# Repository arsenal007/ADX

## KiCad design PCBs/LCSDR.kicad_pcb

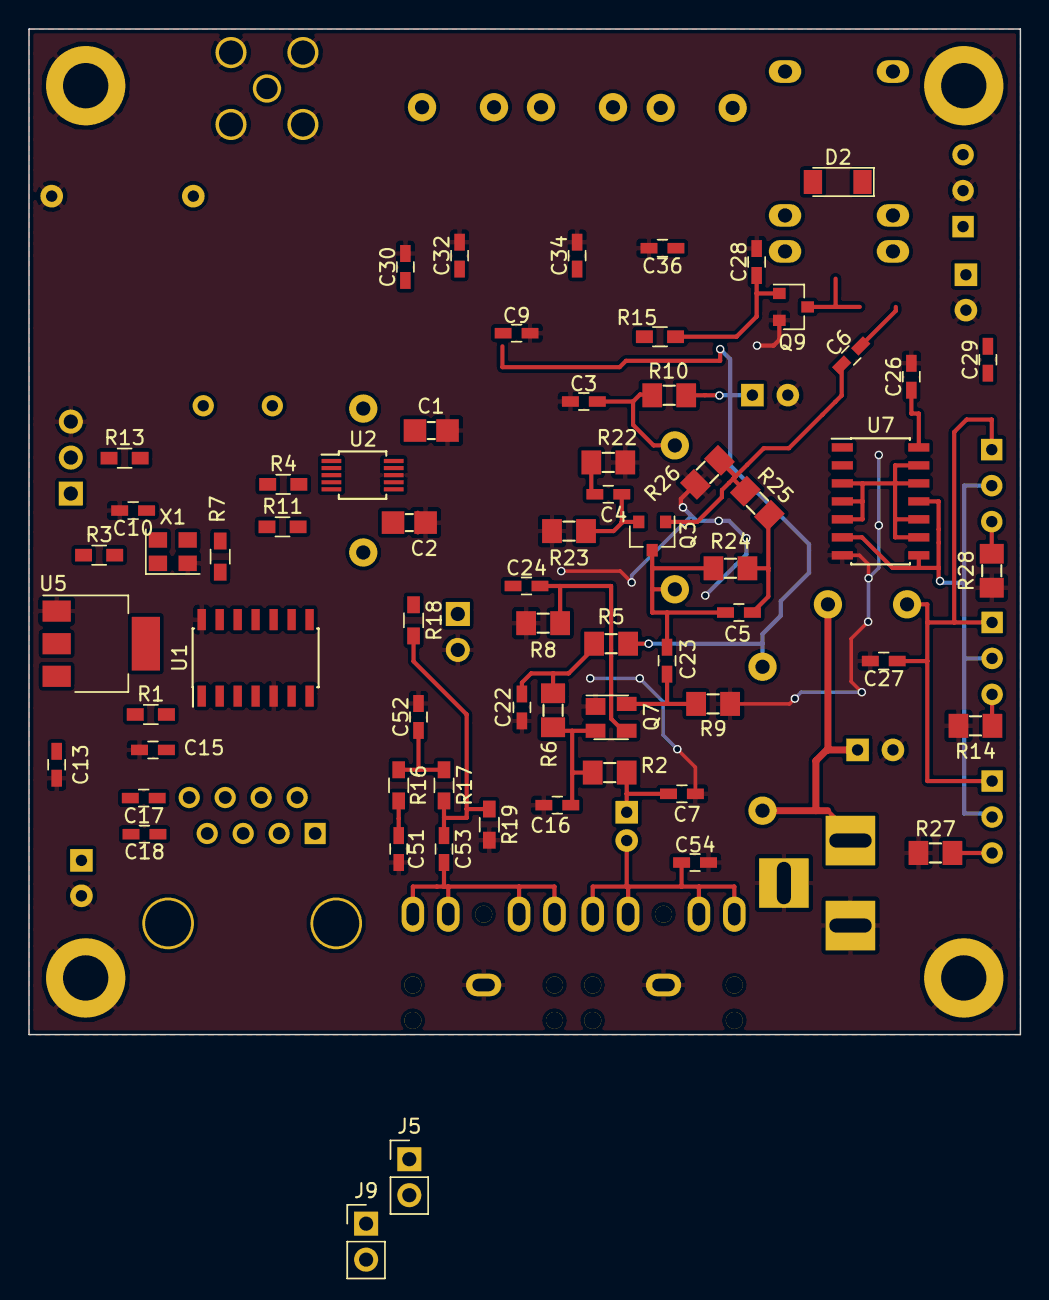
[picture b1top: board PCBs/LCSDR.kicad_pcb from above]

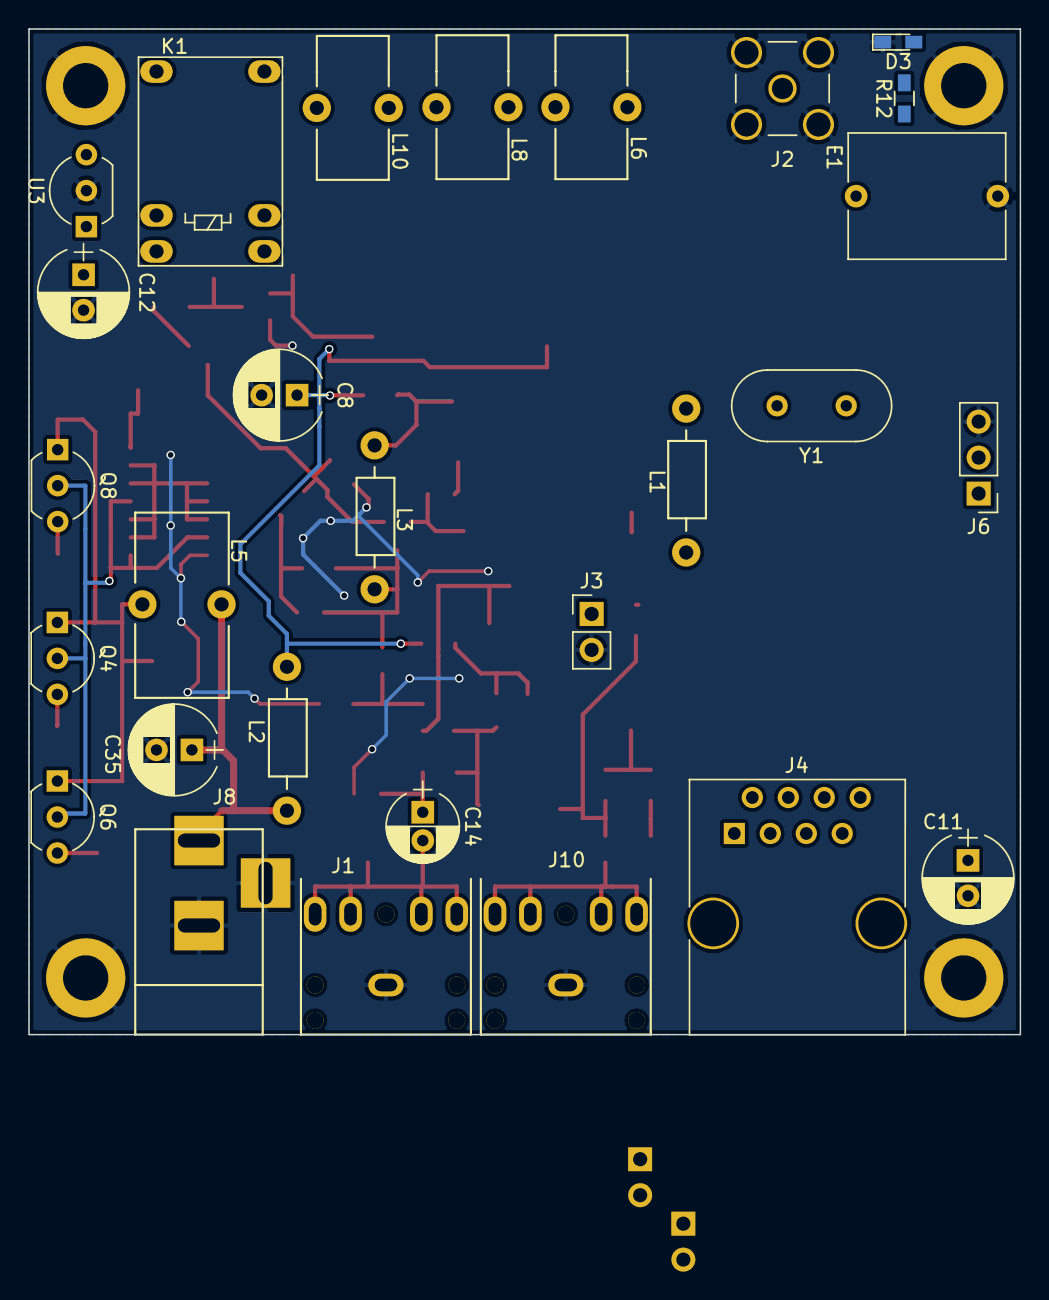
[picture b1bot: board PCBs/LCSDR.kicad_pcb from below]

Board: 2 copper layers, 70.0 x 71.0 mm, 97 parts (28 on the bottom side), 56 nets.

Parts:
C1, C2: 1µF; C_1206_0603
C3, C4, C5, C9, C10, C13, C15, C17, C18, C22, C26, C27, C29, C54: 100nF; C_0603_HandSoldering
C6, C7, C16, C23, C24, C51, C52: 10nF; C_0603_HandSoldering
C8, C11, C12, C35: 100uF; CP_Radial_D6.3mm_P2.50mm
C14: 2.2uF; CP_Radial_D5.0mm_P2.00mm
C28: 15nF; C_0603_HandSoldering
C30, C36: 360pF; C_0603_HandSoldering
C32, C34: 750pF; C_0603_HandSoldering
C53: 1uF; C_0603_HandSoldering
D2: LL4148; D_MiniMELF
D3: LED; LED_0603_HandSoldering
E1: 90V; C_Rect_L11.0mm_W8.8mm_P10.00mm_MKT
J1: MIC; audio_jack_3_5mm_PJ307
J2: ANT; SMA_THT_Jack_Straight
J3: Calibration; Pin_Header_Straight_1x02_Pitch2.54mm
J4: RJ45; RJ45_8
J5, J9: Conn_01x02; Pin_Header_Straight_1x02_Pitch2.54mm
J6: Conn_01x03; Pin_Header_Straight_1x03_Pitch2.54mm
J8: Jack-DC; BARREL_JACK
J10: SPK; audio_jack_3_5mm_PJ307
J12, J13, J14, J15: Conn_01x01; MountingHole_3.2mm_M3_DIN965_Pad
K1: TIANBO-HJR-4102-L; Relay_SPDT_HJR-4102
L1: 100uH; Choke_Horizontal_RM10mm
L2: 33µH; Choke_Horizontal_RM10mm
L3: 5.6uH; Choke_Horizontal_RM10mm
L5: 20uH; Choke_Toroid_6,5x13mm_Vertical
L6, L10: 1.42uH; Choke_Toroid_5x10mm_Vertical
L8: 1.62uH; Choke_Toroid_5x10mm_Vertical
Q3: BFR93A; SOT-23
Q4, Q6, Q8: BS170; TO-92_Inline_Wide
Q7: BF998; SOT-143
Q9: BC849; SOT-23
R1: 0; R_0603_HandSoldering
R2: 2.2K; R_1206_0603
R3, R7, R13: 47; R_0603_HandSoldering
R4, R11: 10K; R_0603_HandSoldering
R5: 100; R_1206_0603
R6: 2.2k; R_1206_0603
R8, R25: 470; R_1206_0603
R9: 27k; R_1206_0603
R10: 33; R_1206_0603
R12: 1k; R_0603_HandSoldering
R14, R27, R28: 1R; R_1206_0603
R15: 3.3k; R_0603_HandSoldering
R16, R17: 10k; R_0603_HandSoldering
R18: 1M; R_0603_HandSoldering
R19: 4.7K; R_0603_HandSoldering
R22: 4.7; R_1206_0603
R23: 47; R_1206_0603
R24: 2.7K; R_1206_0603
R26: 1K; R_1206_0603
U1: ATtiny1614-SS; SOIC-14_3.9x8.7mm_Pitch1.27mm
U2: Si5351; MSOP-10_3x3mm_Pitch0.5mm
U3: L78L05_TO92; TO-92_Inline_Wide
U5: LM1117-3.3; SOT-223-3_TabPin2
U7: 74ACT00; SOIC-14_3.9x8.7mm_Pitch1.27mm
X1: TXC-7C; Oscillator_SMD_Abracon_ASE-4pin_3.2x2.5mm
Y1: 25Mhz; Crystal_HC49-U_Vertical

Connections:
+3V3: C1.1, C10.1, C11.1, C13.1, L1.1, R1.1, R4.1, R11.1, R18.1, U2.1, U5.2, X1.4
+12V: C8.1, C9.1, D2.1, K1.5, L2.1, R5.2, R10.2, U3.3, U5.3
+12VA: C35.1, J8.1, L2.2, L5.1
AUDIO_IN: C51.1, R16.1, U1.4
CLK0: U2.10, U7.1
CLK1: C24.2, U2.9
GND: C1.2, C2.1, C3.2, C7.2, C8.2, C9.2, C10.2, C11.2, C12.2, C13.2, C15.2, C16.2, C22.2, C26.2, C27.2, C28.2, C30.2, C32.2, C34.2, C35.2, C36.2, C51.2, C52.2, C54.2, D3.1, E1.2, J1.1, J2.2, J3.2, J5.2, J6.3, J8.2, J8.3, J9.2, J10.1, J12.1, J13.1, J14.1, J15.1, Q7.1, Q9.2, R8.2, R9.2, R14.2, R19.2, R22.2, R23.2, R26.2, R27.2, R28.2, U1.5, U1.14, U2.8, U3.2, U5.1, U7.7, X1.2
LED: R12.1, U1.3
LPF: C36.1, J9.1, K1.1, K1.12, L10.2
unnamed: C2.2, L1.2, U2.7
unnamed: C3.1, L3.1, R10.1
unnamed: C4.1, R22.1
unnamed: C4.2, Q3.2, R23.1
unnamed: C5.2, R24.2, R25.1
unnamed: C6.1, Q3.1, R25.2, R26.1
unnamed: C7.1, C14.1, R2.2
unnamed: C14.2, C54.1, J1.2, J1.3, J1.4, J1.5
unnamed: C16.1, Q7.2, R2.1, R6.1
unnamed: C17.1, J4.8
unnamed: C18.1, J4.7
unnamed: C22.1, R5.1, R6.2
unnamed: C23.1, Q7.4, R9.1
unnamed: C5.1, C23.2, L3.2, Q3.3, R24.1
unnamed: C24.1, Q7.3, R8.1
unnamed: C27.1, C29.1, L5.2, Q4.1, Q6.1, Q8.1
unnamed: C28.1, Q9.1, R15.1
unnamed: C29.2, K1.6
unnamed: C30.1, E1.1, J2.1, J5.1, L6.1
unnamed: C32.1, L6.2, L8.1
unnamed: C34.1, L8.2, L10.1
unnamed: C52.1, R16.2, R17.1
unnamed: C53.1, J10.2, J10.3, J10.4, J10.5
unnamed: C53.2, R17.2, R18.2, R19.1
unnamed: D2.2, K1.8, Q9.3
unnamed: D3.2, R12.2
unnamed: J3.1, U2.6
unnamed: J4.3, U1.7
unnamed: J4.6, U1.6
unnamed: J6.1, R3.1
unnamed: J6.2, R13.1
unnamed: Q4.2, Q6.2, Q8.2, U7.6, U7.8, U7.11
unnamed: Q4.3, R14.1
unnamed: Q6.3, R27.1
unnamed: Q8.3, R28.1
unnamed: R7.1, U1.13
unnamed: R7.2, X1.3
unnamed: U2.2, Y1.2
unnamed: U2.3, Y1.1
unnamed: U7.3, U7.4, U7.5, U7.9, U7.10, U7.12, U7.13
RESET_UPDI: C17.2, C18.2, R13.2, U1.10
RF_IN: C6.2, K1.7
RX_TX: R15.2, U1.11
RX_TX_PA: U1.12, U7.2
SCL: R4.2, U1.9, U2.4
SDA: R11.2, U1.8, U2.5
VCC: C12.1, C15.1, C26.1, R1.2, R3.2, U1.1, U3.1, U7.14

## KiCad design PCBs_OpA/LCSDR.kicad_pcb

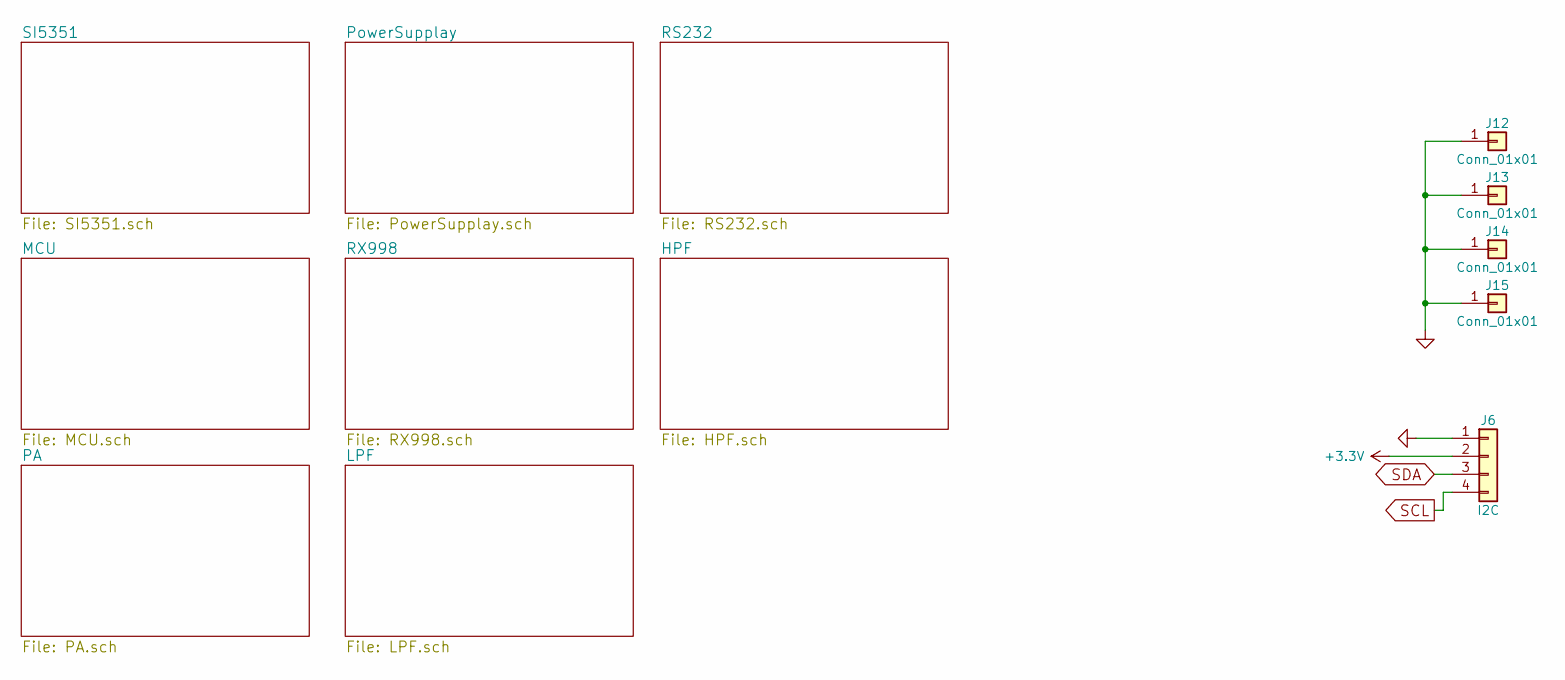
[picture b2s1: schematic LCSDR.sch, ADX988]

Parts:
J6: I2C; Pin_Header_Straight_1x04_Pitch2.54mm
J12, J13, J14, J15: Conn_01x01; MountingHole_3.2mm_M3_DIN965_Pad

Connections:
+3V3: J6.2; also elsewhere on the board
GND: J6.1, J12.1, J13.1, J14.1, J15.1; also elsewhere on the board
SCL: J6.4; also elsewhere on the board
SDA: J6.3; also elsewhere on the board

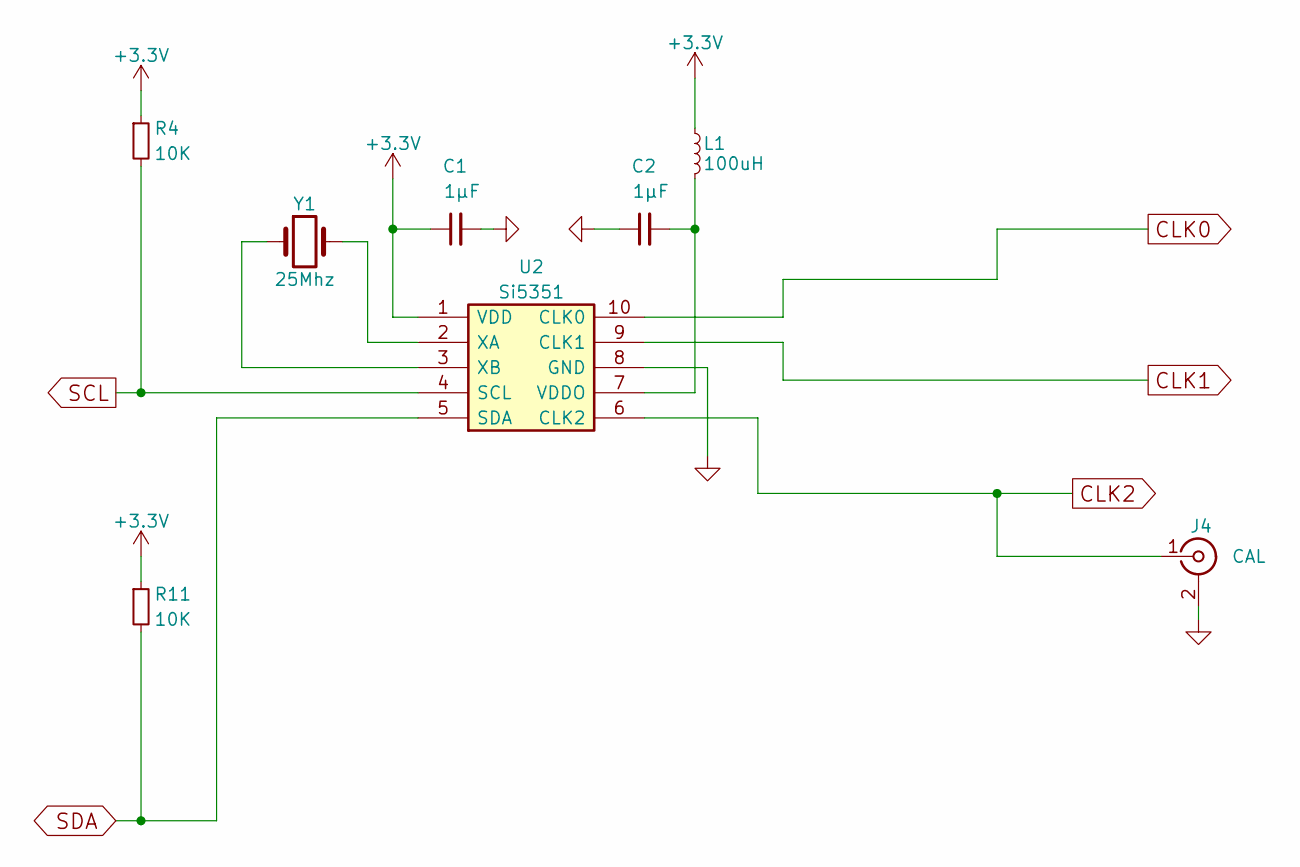
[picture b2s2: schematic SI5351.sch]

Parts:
C1, C2: 1µF; C_1206_0603
J4: CAL; U.FL_Molex_MCRF_73412-0110_Vertical
L1: 100uH; R_Axial_DIN0207_L6.3mm_D2.5mm_P10.16mm_Horizontal
R4, R11: 10K; R_1206_0603
U2: Si5351; MSOP-10_3x3mm_Pitch0.5mm
Y1: 25Mhz; Crystal_SMD_HC49-SD

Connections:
+3V3: C1.1, L1.1, R4.1, R11.1, U2.1 (VDD); also elsewhere on the board
CLK0: U2.10 (CLK0); also elsewhere on the board
CLK1: U2.9 (CLK1); also elsewhere on the board
CLK2: J4.1 (In), U2.6 (CLK2); also elsewhere on the board
GND: C1.2, C2.1, J4.2 (Ext), U2.8 (GND); also elsewhere on the board
unnamed: C2.2, L1.2, U2.7 (VDDO)
unnamed: U2.2 (XA), Y1.2
unnamed: U2.3 (XB), Y1.1
SCL: R4.2, U2.4 (SCL); also elsewhere on the board
SDA: R11.2, U2.5 (SDA); also elsewhere on the board

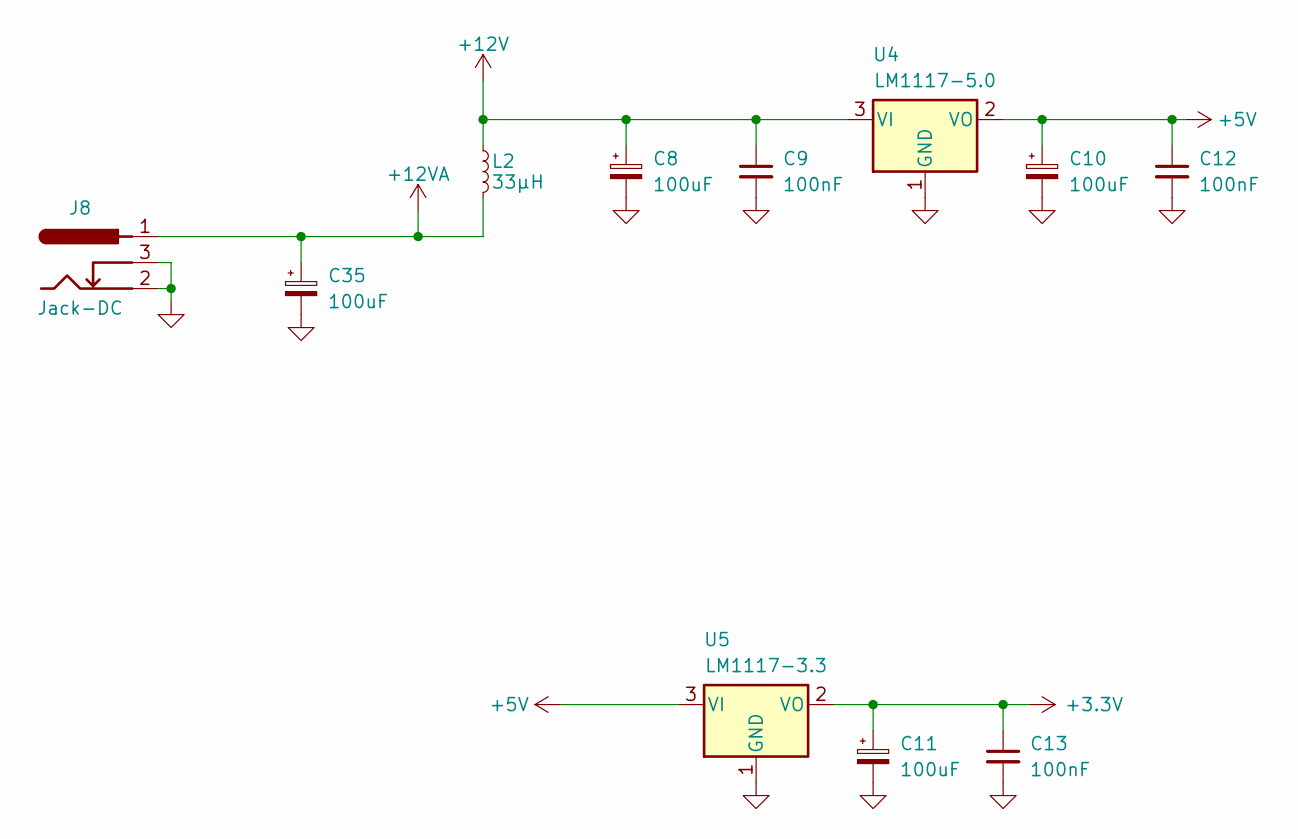
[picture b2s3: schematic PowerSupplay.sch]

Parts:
C8, C10, C11, C35: 100uF; CP_Radial_D6.3mm_P2.50mm
C9, C12, C13: 100nF; C_1206_0603
J8: Jack-DC; BARREL_JACK
L2: 33µH; Choke_Horizontal_RM10mm
U4: LM1117-5.0; SOT-223-3_TabPin2
U5: LM1117-3.3; SOT-223-3_TabPin2

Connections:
+3V3: C11.1, C13.1, U5.2 (VO); also elsewhere on the board
+5V: C10.1, C12.1, U4.2 (VO), U5.3 (VI); also elsewhere on the board
+12V: C8.1, C9.1, L2.1, U4.3 (VI); also elsewhere on the board
+12VA: C35.1, J8.1, L2.2; also elsewhere on the board
GND: C8.2, C9.2, C10.2, C11.2, C12.2, C13.2, C35.2, J8.2, J8.3, U4.1 (GND), U5.1 (GND); also elsewhere on the board

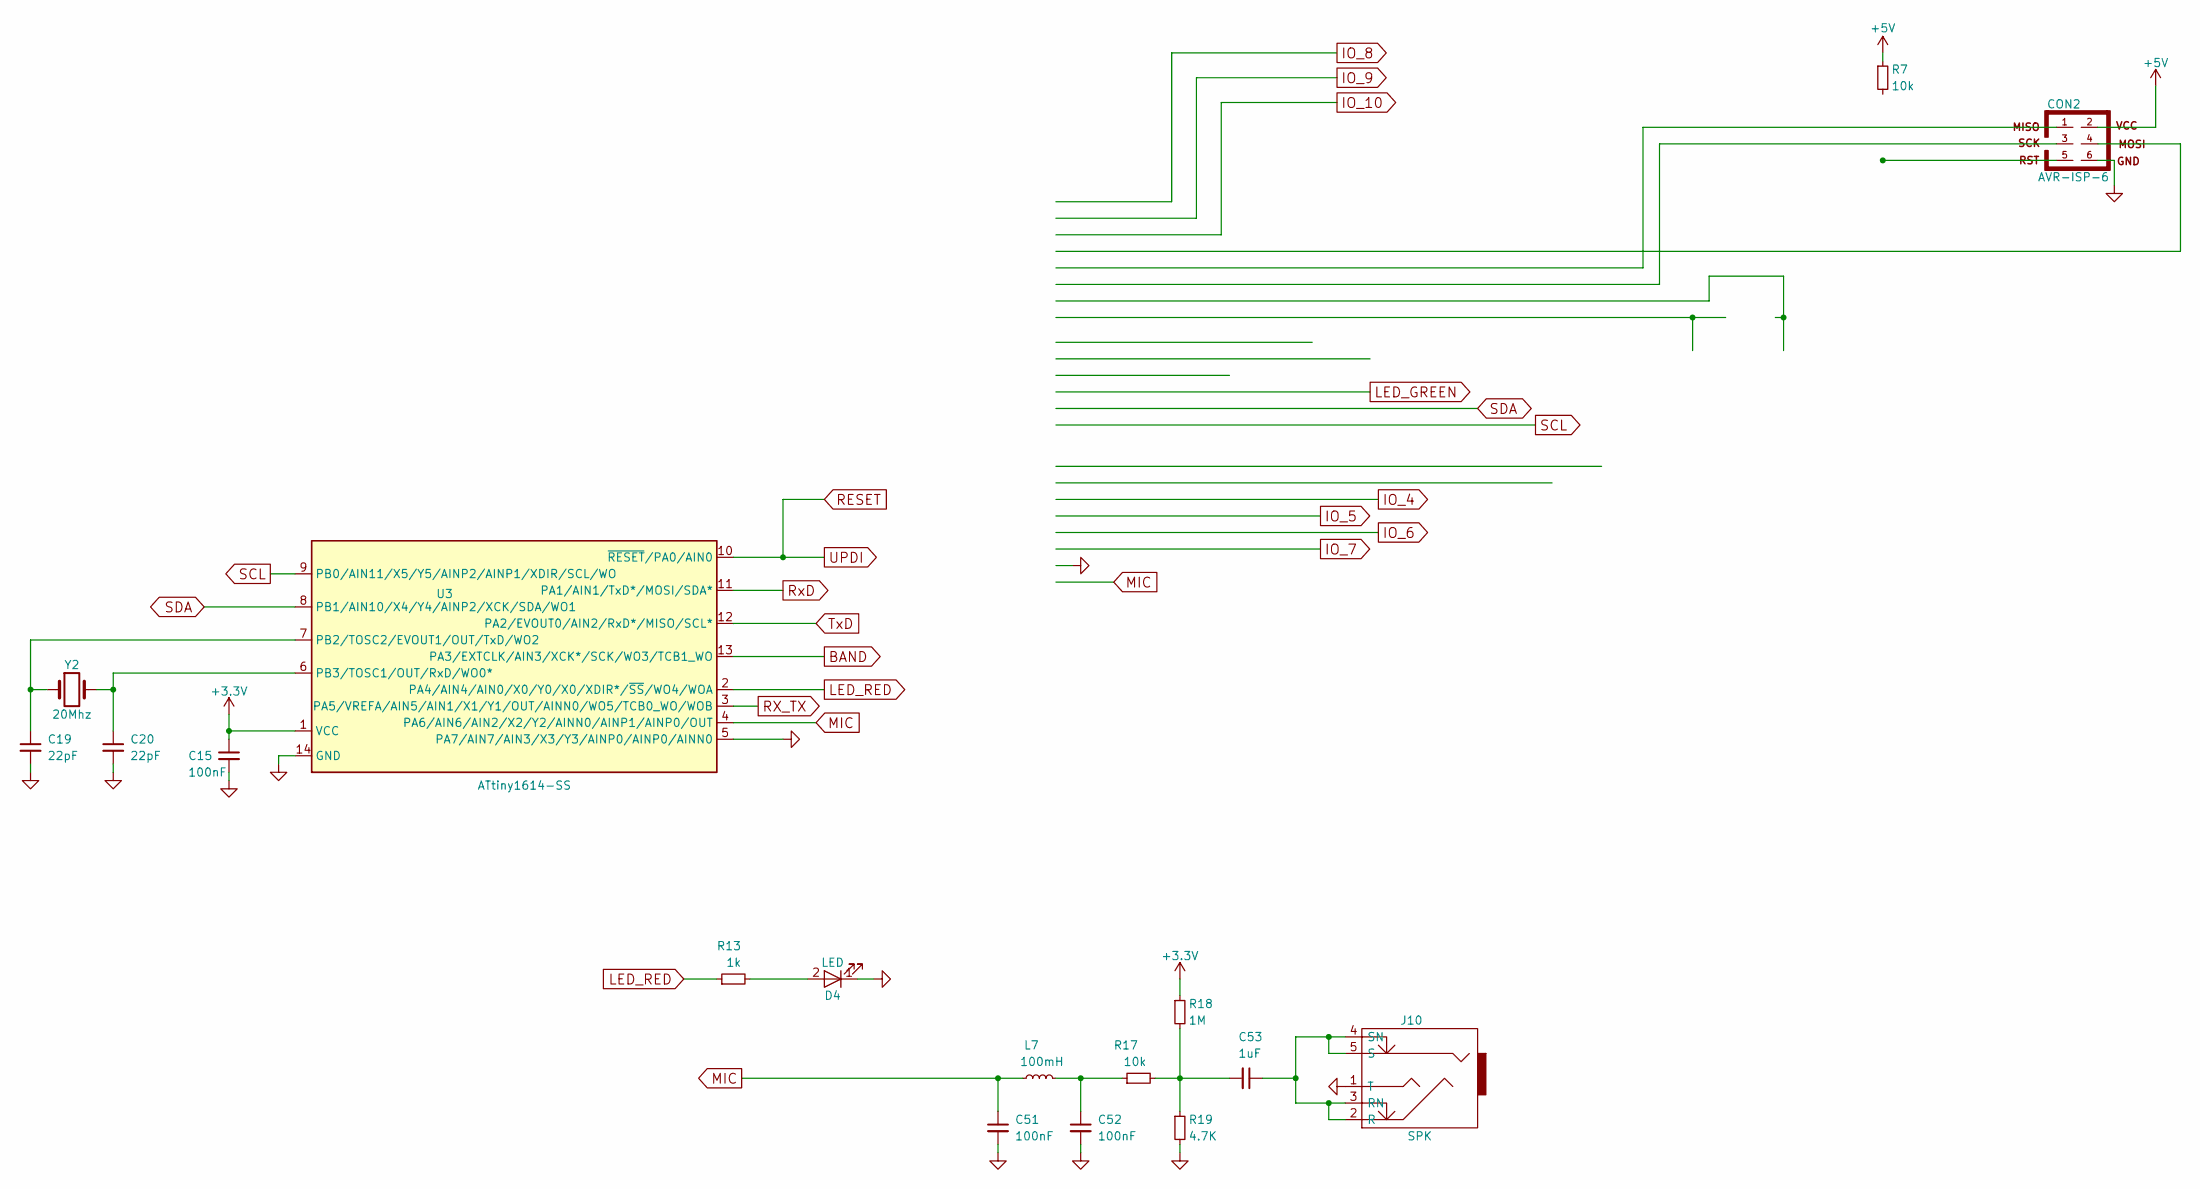
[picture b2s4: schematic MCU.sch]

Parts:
C15, C51, C52: 100nF; C_1206_0603
C19, C20: 22pF; C_1206_0603
C53: 1uF; C_1206_0603
CON2: AVR-ISP-6; IDC-Header_2x03_Pitch2.54mm_Straight
D4: LED; LED_D3.0mm_Horizontal_O3.81mm_Z10.0mm
J10: SPK; audio_jack_3_5mm_PJ307
L7: 100mH; Choke_Toroid_8x16mm_Vertical
R7, R17: 10k; R_1206_0603
R13: 1k; R_1206_0603
R18: 1M; R_1206_0603
R19: 4.7K; R_1206_0603
U3: ATtiny1614-SS; SOIC-14_3.9x8.7mm_Pitch1.27mm
Y2: 20Mhz; Crystal_HC49-U_Vertical

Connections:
+3V3: C15.1, R18.1, U3.1 (VCC); also elsewhere on the board
+5V: CON2.2, R7.1; also elsewhere on the board
GND: C15.2, C19.2, C20.2, C51.2, C52.2, CON2.6, D4.1 (K), J10.1 (T), R19.2, U3.5 (PA7/AIN7/AIN3/X3/Y3/AINP0/AINP0/AINN0), U3.14 (GND); also elsewhere on the board
LED_RED: R13.1, U3.2 (PA4/AIN4/AIN0/X0/Y0/X0/XDIR*/~SS~/WO4/W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)
MIC: C51.1, L7.1, U3.4 (PA6/AIN6/AIN2/X2/Y2/AINN0/AINP1/AINP0/O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)
unnamed: C19.1, U3.7 (PB2/TOSC2/EVOUT1/OUT/TxD/WO2), Y2.1
unnamed: C20.1, U3.6 (PB3/TOSC1/OUT/RxD/WO0*), Y2.2
unnamed: C52.1, L7.2, R17.1
unnamed: C53.1, J10.2 (R), J10.3 (RN), J10.4 (SN), J10.5 (S)
unnamed: C53.2, R17.2, R18.2, R19.1
unnamed: D4.2 (A), R13.2
RESET: U3.10 (~RESET~/PA0/AIN0); also elsewhere on the board
RX_TX: U3.3 (PA5/VREFA/AIN5/AIN1/X1/Y1/OUT/AINN0/WO5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); also elsewhere on the board
RxD: U3.11 (PA1/AIN1/TxD*/MOSI/SDA*); also elsewhere on the board
SCL: U3.9 (PB0/AIN11/X5/Y5/AINP2/AINP1/XDIR/SCL/WO); also elsewhere on the board
SDA: U3.8 (PB1/AIN10/X4/Y4/AINP2/XCK/SDA/WO1); also elsewhere on the board
TxD: U3.12 (PA2/EVOUT0/AIN2/RxD*/MISO/SCL*); also elsewhere on the board

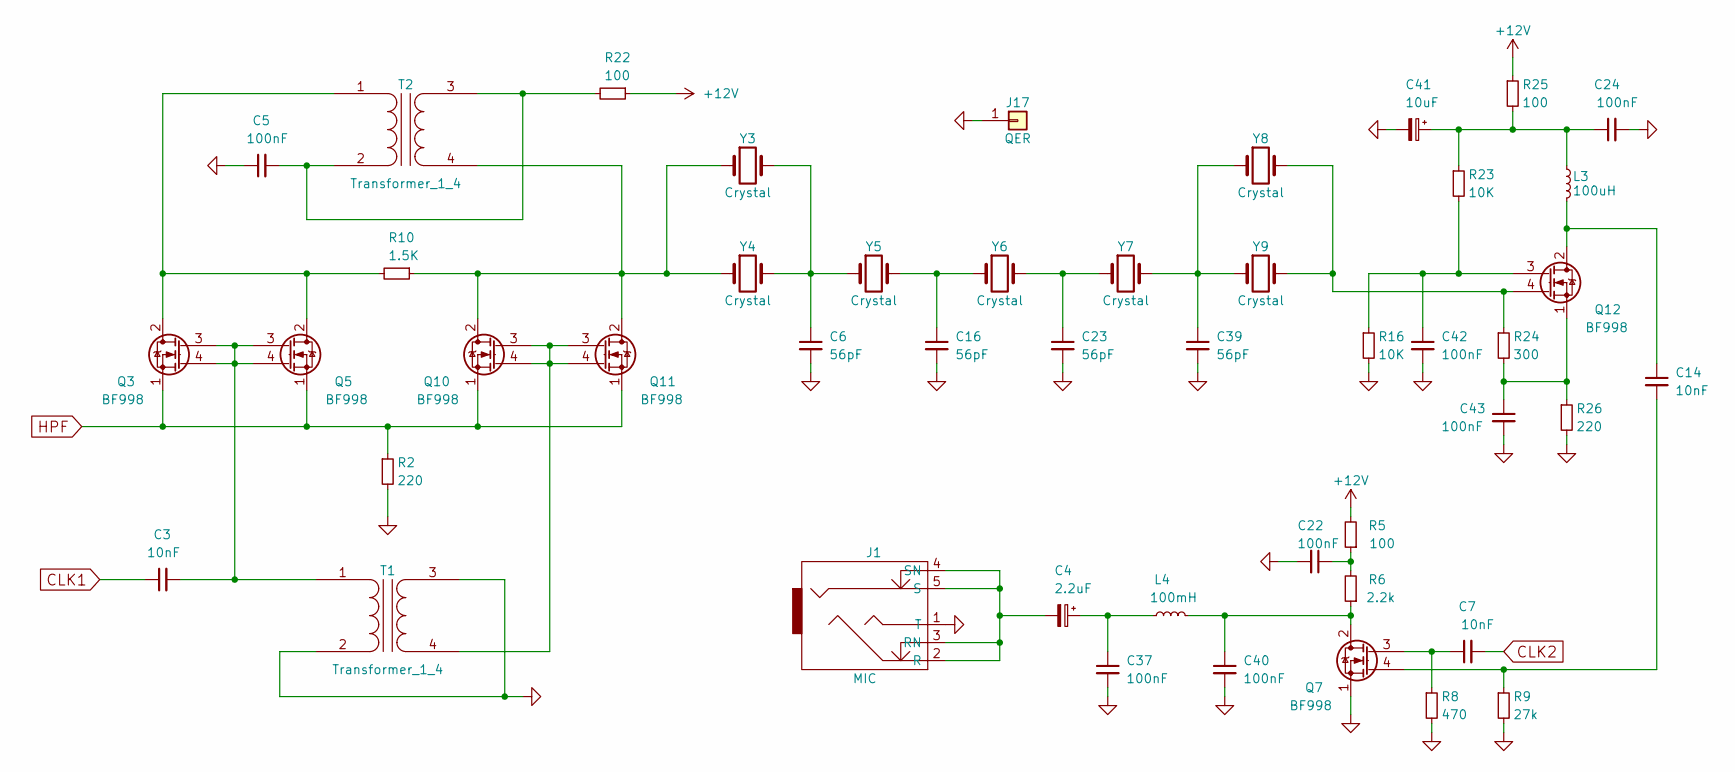
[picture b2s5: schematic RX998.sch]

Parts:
C3, C7, C14: 10nF; C_1206_0603
C4: 2.2uF; CP_Radial_D5.0mm_P2.00mm
C5, C22, C24, C37, C40, C42, C43: 100nF; C_1206_0603
C6, C16, C23, C39: 56pF; C_1206_0603
C41: 10uF; CP_Radial_D5.0mm_P2.00mm
J1: MIC; audio_jack_3_5mm_PJ307
J17: QER; Pin_Header_Straight_1x01_Pitch2.54mm
L3: 100uH; Choke_Horizontal_RM10mm
L4: 100mH; Choke_Toroid_8x16mm_Vertical
Q3, Q5, Q7, Q10, Q11, Q12: BF998; SOT-143
R2, R26: 220; R_1206_0603
R5, R22, R25: 100; R_1206_0603
R6: 2.2k; R_1206_0603
R8: 470; R_1206_0603
R9: 27k; R_1206_0603
R10: 1.5K; R_1206_0603
R16, R23: 10K; R_1206_0603
R24: 300; R_1206_0603
T1, T2: Transformer_1_4; TF14
Y3, Y4, Y5, Y6, Y7, Y8, Y9: Crystal; Crystal_HC49-U_Vertical

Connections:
+12V: R5.2, R22.1, R25.1; also elsewhere on the board
CLK1: C3.1; also elsewhere on the board
CLK2: C7.2; also elsewhere on the board
GND: C5.1, C6.2, C16.2, C22.2, C23.2, C24.2, C37.2, C39.2, C40.2, C41.2, C42.2, C43.2, J1.1 (T), J17.1, Q7.1 (S), R2.2, R8.2, R9.2, R16.2, R26.2, T1.2 (AB), T1.3; also elsewhere on the board
HPF: Q3.1 (S), Q5.1 (S), Q10.1 (S), Q11.1 (S), R2.1; also elsewhere on the board
unnamed: C3.2, Q3.3 (G2), Q3.4 (G1), Q5.3 (G2), Q5.4 (G1), T1.1 (AA)
unnamed: C4.2, J1.2 (R), J1.3 (RN), J1.4 (SN), J1.5 (S)
unnamed: C5.2, R22.2, T2.2 (AB), T2.3
unnamed: C6.1, Y3.2, Y4.2, Y5.1
unnamed: C7.1, Q7.3 (G2), R8.1
unnamed: C14.1, L3.2, Q12.2 (D)
unnamed: C14.2, Q7.4 (G1), R9.1
unnamed: C16.1, Y5.2, Y6.1
unnamed: C22.1, R5.1, R6.2
unnamed: C23.1, Y6.2, Y7.1
unnamed: C24.1, C41.1, L3.1, R23.1, R25.2
unnamed: C4.1, C37.1, L4.1
unnamed: C39.1, Y7.2, Y8.1, Y9.1
unnamed: C40.1, L4.2, Q7.2 (D), R6.1
unnamed: C42.1, Q12.3 (G2), R16.1, R23.2
unnamed: C43.1, Q12.1 (S), R24.2, R26.1
unnamed: Q3.2 (D), Q5.2 (D), R10.2, T2.1 (AA)
unnamed: Q10.2 (D), Q11.2 (D), R10.1, T2.4, Y3.1, Y4.1
unnamed: Q10.3 (G2), Q10.4 (G1), Q11.3 (G2), Q11.4 (G1), T1.4
unnamed: Q12.4 (G1), R24.1, Y8.2, Y9.2

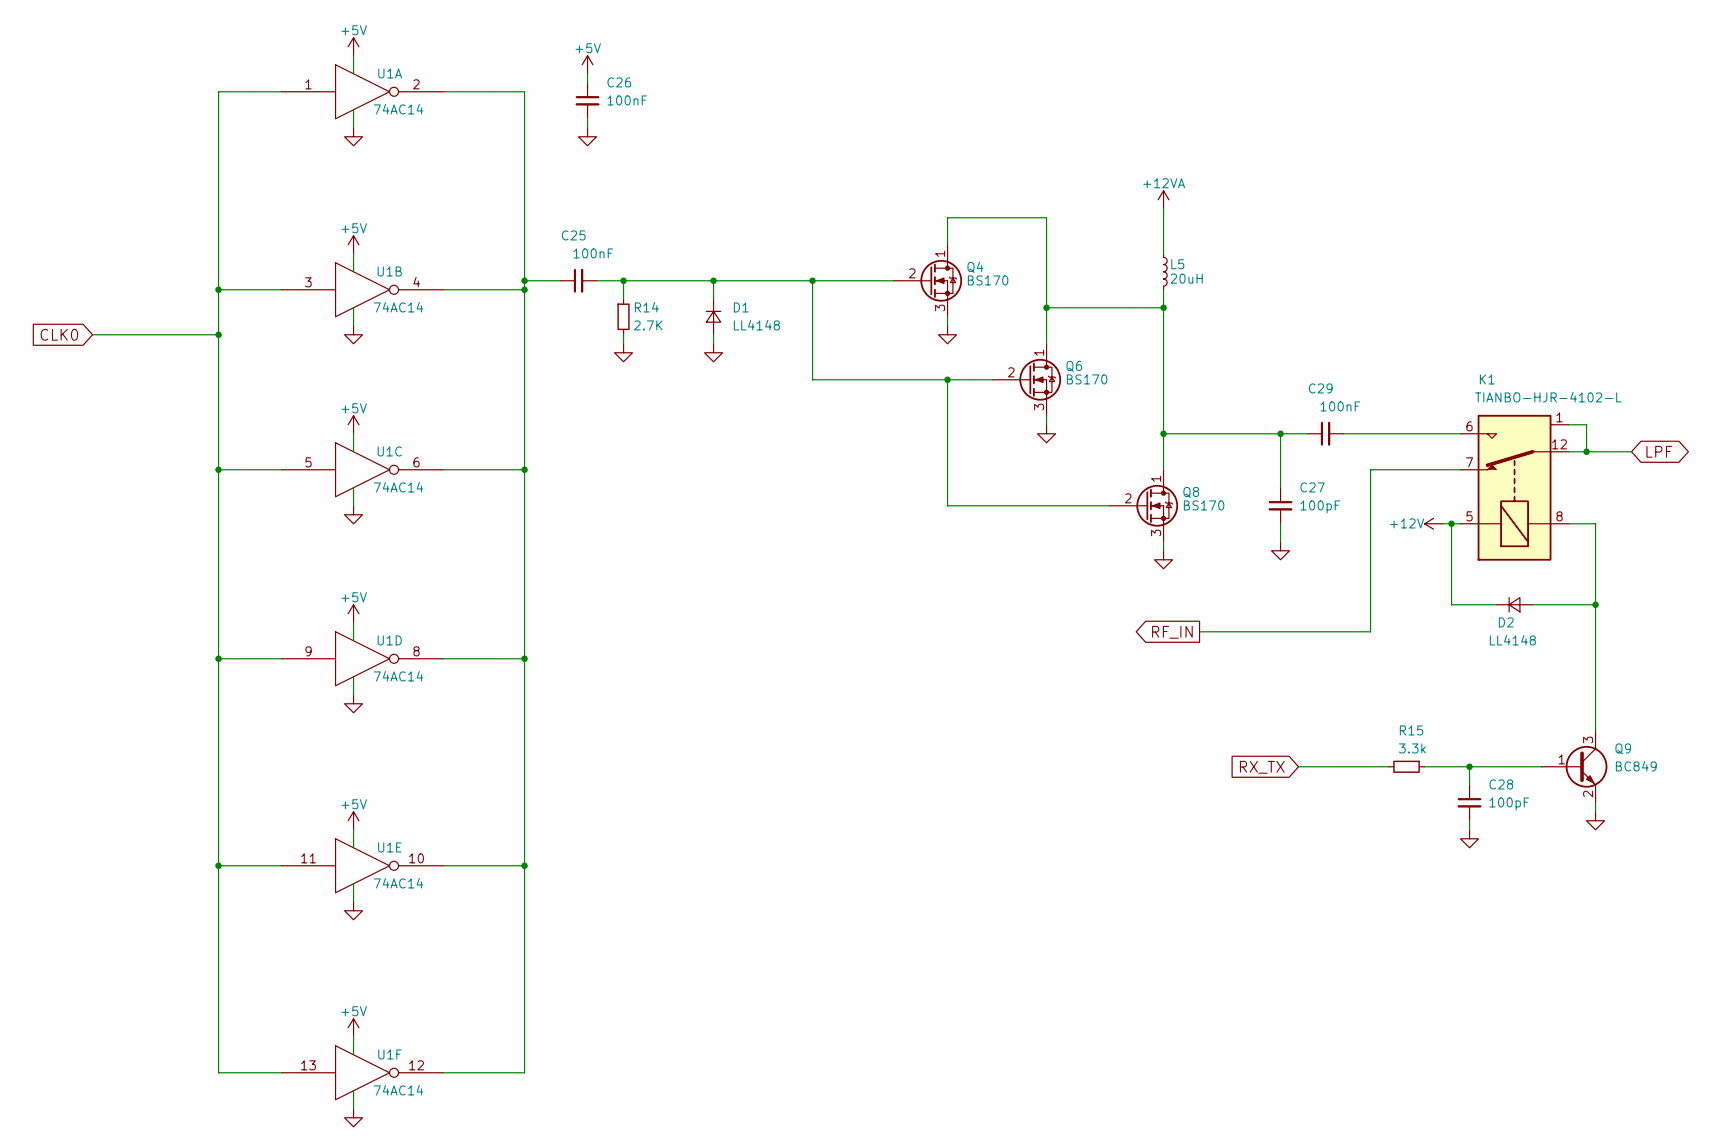
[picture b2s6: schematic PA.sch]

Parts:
C25, C26, C29: 100nF; C_1206_0603
C27: 100pF; C_Disc_D4.7mm_W2.5mm_P5.00mm
C28: 100pF; C_1206_0603
D1, D2: LL4148; D_MiniMELF
K1: TIANBO-HJR-4102-L; Relay_SPDT_HJR-4102
L5: 20uH; Choke_Toroid_6,5x13mm_Vertical
Q4, Q6, Q8: BS170; TO-92_Inline_Wide
Q9: BC849; SOT-23
R14: 2.7K; R_1206_0603
R15: 3.3k; R_1206_0603
U1: 74AC14; DIP-14_W7.62mm_LongPads

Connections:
+5V: C26.1, U1.14 (VCC); also elsewhere on the board
+12V: D2.1 (K), K1.5; also elsewhere on the board
+12VA: L5.1; also elsewhere on the board
CLK0: U1.1, U1.3, U1.5, U1.9, U1.11, U1.13; also elsewhere on the board
GND: C26.2, C27.2, C28.2, D1.2 (A), Q4.3 (S), Q6.3 (S), Q8.3 (S), Q9.2 (E), R14.2, U1.7 (GND); also elsewhere on the board
LPF: K1.1, K1.12; also elsewhere on the board
unnamed: C25.1, U1.2, U1.4, U1.6, U1.8, U1.10, U1.12
unnamed: C25.2, D1.1 (K), Q4.2 (G), Q6.2 (G), Q8.2 (G), R14.1
unnamed: C27.1, C29.1, L5.2, Q4.1 (D), Q6.1 (D), Q8.1 (D)
unnamed: C28.1, Q9.1 (B), R15.1
unnamed: C29.2, K1.6
unnamed: D2.2 (A), K1.8, Q9.3 (C)
RF_IN: K1.7; also elsewhere on the board
RX_TX: R15.2; also elsewhere on the board

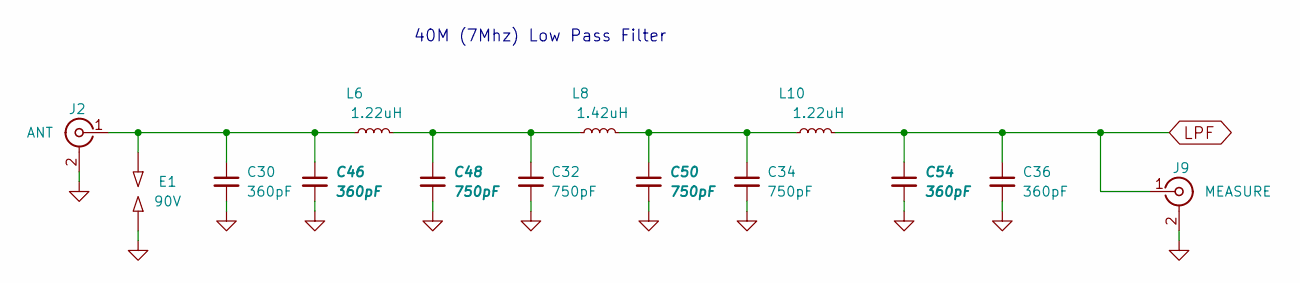
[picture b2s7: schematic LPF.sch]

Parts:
C30, C36: 360pF; C_Disc_D4.7mm_W2.5mm_P5.00mm
C32, C34: 750pF; C_Disc_D4.7mm_W2.5mm_P5.00mm
C46, C54: 360pF; C_1206_0603
C48, C50: 750pF; C_1206_0603
E1: 90V; C_Rect_L11.0mm_W8.8mm_P10.00mm_MKT
J2: ANT; SMA_THT_Jack_Straight
J9: MEASURE; U.FL_Molex_MCRF_73412-0110_Vertical
L6, L10: 1.22uH; Choke_Toroid_6,5x13mm_Vertical
L8: 1.42uH; Choke_Toroid_6,5x13mm_Vertical

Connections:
GND: C30.2, C32.2, C34.2, C36.2, C46.2, C48.2, C50.2, C54.2, E1.2, J2.2 (Ext), J9.2 (Ext); also elsewhere on the board
LPF: C36.1, C54.1, J9.1 (In), L10.2; also elsewhere on the board
unnamed: C30.1, C46.1, E1.1, J2.1 (In), L6.1
unnamed: C32.1, C48.1, L6.2, L8.1
unnamed: C34.1, C50.1, L8.2, L10.1

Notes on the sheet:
40M (7Mhz) Low Pass Filter

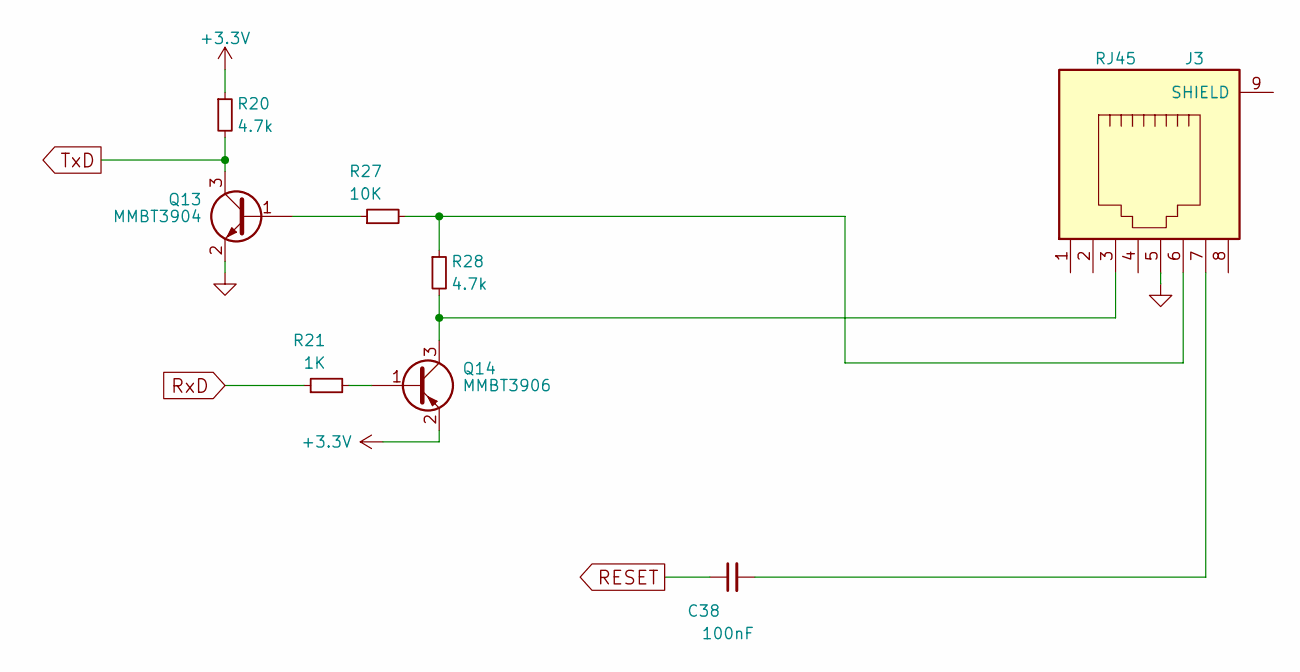
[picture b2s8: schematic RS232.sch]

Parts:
C38: 100nF; C_1206_0603
J3: RJ45; RJ45_8
Q13: MMBT3904; SOT-23
Q14: MMBT3906; SOT-23
R20, R28: 4.7k; R_0603_HandSoldering
R21: 1K; R_0603_HandSoldering
R27: 10K; R_0603_HandSoldering

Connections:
+3V3: Q14.2 (E), R20.1; also elsewhere on the board
GND: J3.5, Q13.2 (E); also elsewhere on the board
unnamed: C38.2, J3.7
unnamed: J3.3, Q14.3 (C), R28.2
unnamed: J3.6, R27.2, R28.1
unnamed: Q13.1 (B), R27.1
unnamed: Q14.1 (B), R21.2
RESET: C38.1; also elsewhere on the board
RxD: R21.1; also elsewhere on the board
TxD: Q13.3 (C), R20.2; also elsewhere on the board

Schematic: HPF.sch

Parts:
C21, C49: 680pF; C_1206_0603
C45, C47: 270pF; C_1206_0603
J5, J7: MEASURE; U.FL_Molex_MCRF_73412-0110_Vertical
L13, L17: 900nH; Choke_Toroid_6,5x13mm_Vertical
L15: 800nH; Choke_Toroid_6,5x13mm_Vertical

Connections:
GND: J5.2 (Ext), J7.2 (Ext), L13.2, L15.2, L17.2; also elsewhere on the board
HPF: C49.2, J7.1 (In); also elsewhere on the board
unnamed: C21.2, C45.1, L13.1
unnamed: C45.2, C47.1, L15.1
unnamed: C47.2, C49.1, L17.1
RF_IN: C21.1, J5.1 (In); also elsewhere on the board

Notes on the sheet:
40M (7Mhz) High Pass Filter

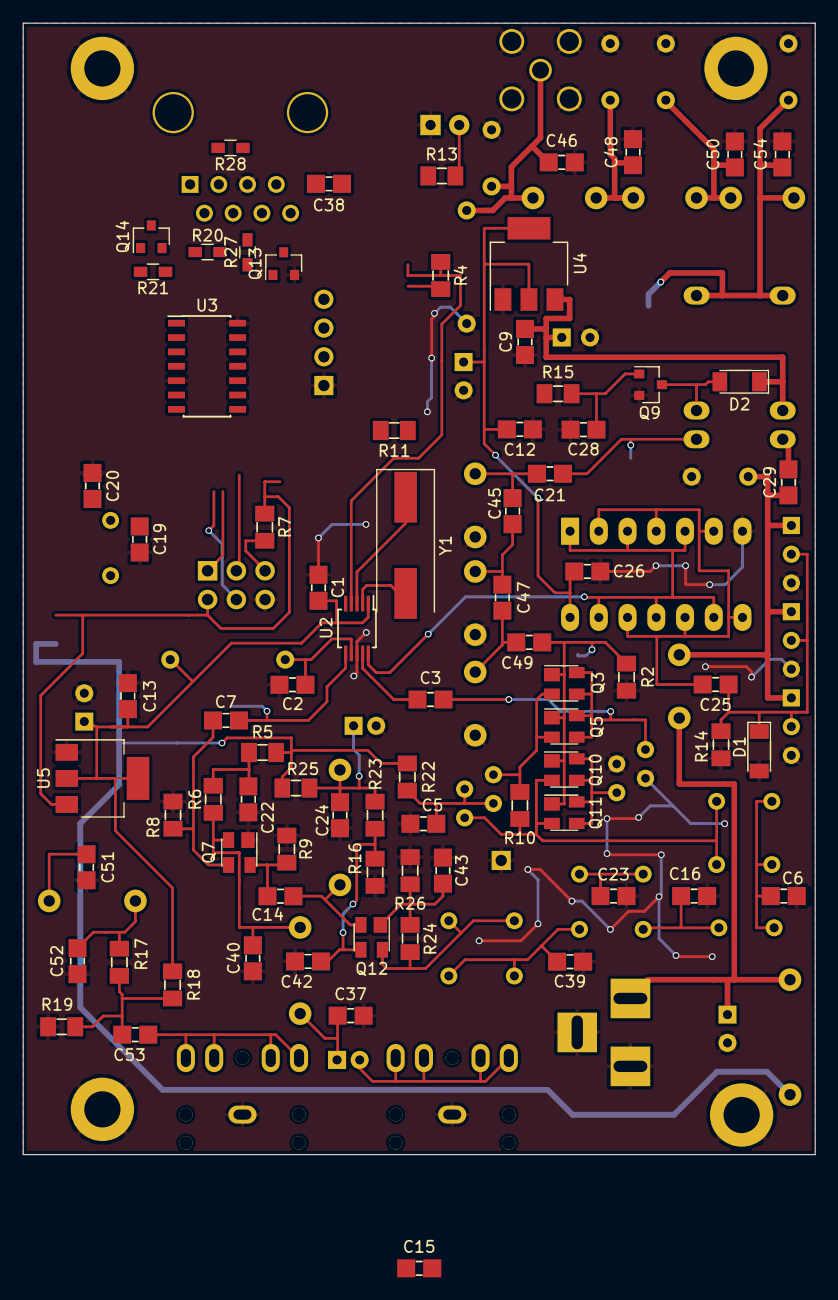
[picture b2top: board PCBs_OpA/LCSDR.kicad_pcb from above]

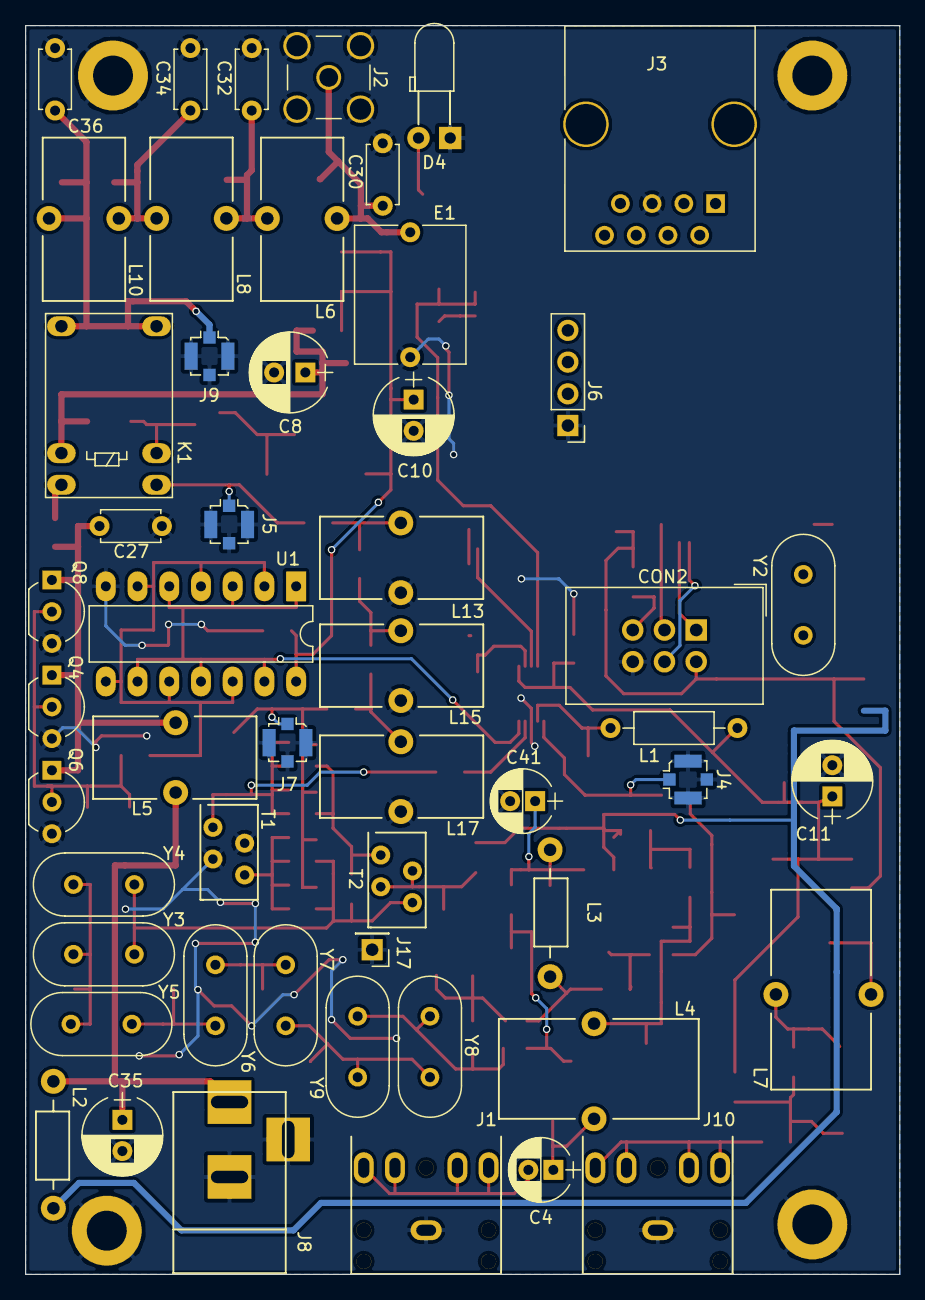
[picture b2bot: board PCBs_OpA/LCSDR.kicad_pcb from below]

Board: 2 copper layers, 70.0 x 100.0 mm, 135 parts (52 on the bottom side), 65 nets.
